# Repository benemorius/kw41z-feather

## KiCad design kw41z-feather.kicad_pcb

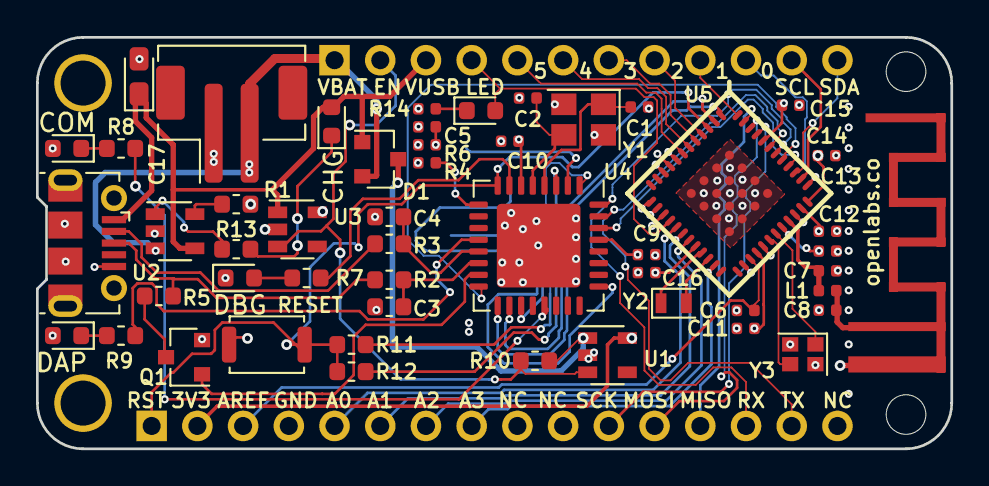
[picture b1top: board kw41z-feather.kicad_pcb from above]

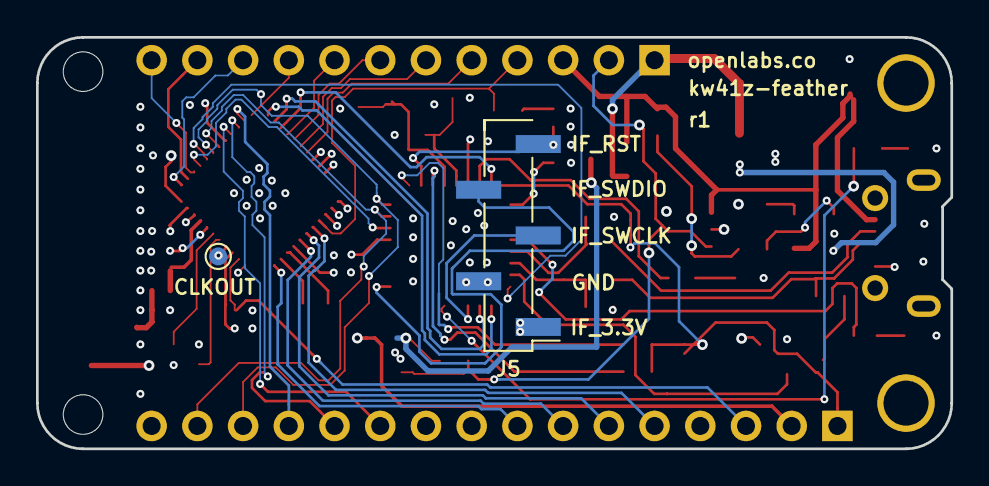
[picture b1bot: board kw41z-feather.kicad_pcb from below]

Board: 4 copper layers, 50.8 x 22.9 mm, 55 parts (2 on the bottom side), 62 nets.

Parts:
ANT1: 2.4GHz; ANT_2_4_GHZ_MEANDERED_F_FLIP
C1, C2: 18pF; C_0402_1005Metric
C3, C4: 18pF; C_0603_1608Metric
C5, C6, C9, C10, C11, C12, C13, C14, C15, C16: 1uF; C_0402_1005Metric
C7: 0.7pF; C_0402_1005Metric
C8: NL; C_0402_1005Metric
C17: 10uF; CP_EIA-2012-15_AVX-P_Pad1.30x1.05mm_HandSolder
D1: D_Schottky_x2_KCom_AAK; SOT-23
D2: CHG; LED_0603_1608Metric
D3, D6: DBG; LED_0603_1608Metric
D4: COM; LED_0603_1608Metric
D5: DAP; LED_0603_1608Metric
J1: BATT; JST_PH_B2B-PH-SM4-TB_1x02-1MP_P2.00mm_Vertical
J2: USB; USB_Micro-B_Molex-105017-0001
J3: Conn_Left; PinSocket_1x16_P2.54mm_Vertical
J4: Conn_Right; PinSocket_1x12_P2.54mm_Vertical
J5: Conn_01x05; PinHeader_1x05_P2.54mm_Vertical_SMD_Pin1Left
L1: 5.1nH; L_0402_1005Metric
Q1: BSS84; SOT-23
R1: 10K; R_0603_1608Metric
R2, R3, R11, R12: 33R; R_0603_1608Metric
R4, R6: 10k; R_0402_1005Metric
R5: 1k5; R_0603_1608Metric
R7, R8, R9: 4k7; R_0603_1608Metric
R10: 10M; R_0603_1608Metric
R13: 1k; R_0603_1608Metric
R14: 4k7; R_0402_1005Metric
SW1: RESET; SW_Push_SPST_NO_Alps_SKRK
TP1: XTAL_OUT; TestPoint_Pad_D1.0mm
U1, U3: SPX3819M5-L-3-3; SOT-23-5
U2: MCP73831-2-OT; SOT-23-5
U4: LPC11U35FHI33_501; QFN-32-1EP_7x7mm_P0.65mm_EP4.65x4.65mm
U5: MKW41Z512VHT4; QFN-48_7_EP_45
Y1: 12MHZ; Crystal_SMD_3225-4Pin_3.2x2.5mm
Y2: 32768Hz; Crystal_SMD_2012-2Pin_2.0x1.2mm
Y3: 32MHz; Crystal_SMD_2016-4Pin_2.0x1.6mm

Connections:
+3.3V_IF: C9.1, C10.1, D4.2, D5.2, J5.1, Q1.2, R4.2, R6.2, U3.5, U4.6, U4.29
+3V3: C11.2, C12.2, C13.2, C14.2, C15.2, C16.2, J3.2, U1.5, U5.9, U5.10, U5.14, U5.15, U5.20, U5.28, U5.32, U5.35, U5.36, U5.44
+BATT: D1.2, J1.2, J4.1, U2.3
+VUSB: C17.1, D1.1, D2.2, J2.1, J4.3, U2.4, U3.1
/0: J4.10, U5.37
/1: J4.9, U5.48
/2: J4.8, U5.4
/3: J4.7, U5.5
/4: J4.6, U5.6
/5: J4.5, U5.7
/A0: J3.5, U5.17
/A1: J3.6, U5.18
/A2: J3.7, U5.19
/A3: J3.8, U5.23
/AREF: C6.2, J3.3, U5.27
/CHG: R13.2, U2.1
/D+: J2.3, R2.2, R5.2
/D-: J2.2, R3.1
/EN: J4.2, R10.1, U1.3, U3.3
/LED: D6.2, J4.4, U5.16
/MISO: J3.13, U5.47
/MOSI: J3.12, U5.46
/PROG: R1.2, U2.5
/SCK: J3.11, U5.45
/SCL: J4.11, U5.38
/SDA: J4.12, U5.39
/TGT_VIN: D1.3, R10.2, U1.1
GND: C1.1, C2.2, C3.2, C4.1, C5.2, C6.1, C7.2, C8.2, C9.2, C10.2, C11.1, C12.1, C13.1, C14.1, C15.1, C16.1, C17.2, D3.1, J1.1, J2.5, J2.6, J3.4, J5.2, R1.1, R14.1, SW1.2, U1.2, U2.2, U3.2, U4.33, U5.8, U5.13, U5.26, U5.34, U5.49, Y1.2, Y1.4, Y3.2, Y3.4
IF_RST: C5.1, J5.5, R6.1, U4.2
IF_SWCLK: J5.3, U4.19
IF_SWDIO: J5.4, U4.25
LED_COM_GREEN: R8.1, U4.21
LED_DAP_BLUE: R9.1, U4.12
LED_PWR_RED: R7.1, U4.7
unnamed: ANT1.1, C8.1, L1.2
unnamed: C1.2, U4.4, Y1.1
unnamed: C2.1, U4.5, Y1.3
unnamed: C7.1, L1.1, U5.33
unnamed: D2.1, R13.1
unnamed: D3.2, R7.2
unnamed: D4.1, R8.2
unnamed: D5.1, R9.2
unnamed: D6.1, R14.2
unnamed: Q1.3, R5.1
unnamed: R4.1, U4.9
unnamed: TP1.1, U5.29
unnamed: U5.21, Y2.1
unnamed: U5.22, Y2.2
unnamed: U5.30, Y3.3
unnamed: U5.31, Y3.1
TGT_CTS: U4.30, U5.40
TGT_NRESET: J3.1, R11.2, R12.2, SW1.1, U4.8, U5.3
TGT_NRESET_FB: R12.1, U4.3
TGT_NRESET_FB_ISP: R11.1, U4.1
TGT_RTS: U4.16, U5.41
TGT_RX: J3.14, U4.32, U5.42
TGT_SWCLK: U4.18, U5.2
TGT_SWDIO: U4.17, U5.1
TGT_TX: J3.15, U4.31, U5.43
USB_DN: C4.2, R3.2, U4.13
USB_DP: C3.1, R2.1, U4.14
USB_SCON: Q1.1, U4.15
